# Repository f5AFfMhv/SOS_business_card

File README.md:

# SOS Business Card PCB

This project was conceived for the [Hackaday 2024 Business Card Contest](https://hackaday.io/contest/195949-2024-business-card-contest). The idea was to create a logical circuit from discrete components that would generate a SOS signal in Morse code. I wanted to make this project a learning experience for creating logical circuits in a simple and practical way.

## Logical Circuit Design

Morse code has following rules for signaling:

- dot is 1 time unit
- dash is 3 time units
- the space between symbols of the same letter is 1 time unit
- the space between words is 7 time units.

Following these rules SOS signal timing diagram will look like this:

> Diagram is made with [wavedrom online tool](https://wavedrom.com/editor.html). You can import json file from `Design/Wavedrom` for modifications.

We see that 34 independent logical states are needed. This introduces a problem as we could reduce logical circuit complexity by using 32 states instead as it will require 5 inputs for our truth table $(2^5=32)$.

I decided to violate last Morse code signaling rule and use 5 time units for spacing between words instead of 7.

I'm using [Logism](http://www.cburch.com/logisim/), it can take truth table as input and generate logical circuit. You can find Logism circuit files in `Design/Logism` directory. Generated circuit is not perfect and can be improved manually (by removing duplicated components and changing number of inputs for logical gates).

<div align="center">
    
</div>

## Clock Circuit Design

For clock signal I'm using 555 timer. There are lots of tools online for calculating 555 timer circuit parameters. I used [555 Astable Circuit Calculator ](https://ohmslawcalculator.com/555-astable-calculator) for this.

General rules are:

- choose R2 value much higher than R1 for 50% duty cycle;
- C9 sets clock frequency. 330nF capacitor will generate 2Hz signal. To increase frequency, decrease C9 value.

<div align="center">
    
</div>

For generating 5-bit logic circuit input signal we'll need binary counter. It will divide clock signal frequency by 2/4/8/16 and so on.

Full circuit simulation with 555 clock generator, binary counter and logical circuit was done using [Falstad](https://tinyurl.com/2bdrotlr). If link doesn't work, you can find Falstad circuit file in `Design/Falstad` directory.

## Power

Circuit will have 2 power options:

- CR2025 coin battery
- USB-C 5V@3A

USB-C socket CC lines are connected to ground via 5.1K ohm resistor. This tells power source to supply 5V on VBUS line. Most ICs I chose have maximum supply voltage of 6V.

## Output

The circuit will have a small on-board LED for SOS signal output. Additionally, a high-side PMOS load switch can be connected to a larger load, such as a 12V lamp. An external power supply with a maximum of 40V will be needed for this.

<div align="center">
    
</div>

## PCB Design

PCB is designed using KiCAD. All project and gerber files are in `KiCAD` directory.
Full [schematic](schematic.pdf) exported as pdf.

There are some custom symbols and footprints used in this project. Those can be imported from [this](https://github.com/f5AFfMhv/my-kicad-libraries) github repository.

## Finished Project

<div align="center">
    
</div>

Youtube video.

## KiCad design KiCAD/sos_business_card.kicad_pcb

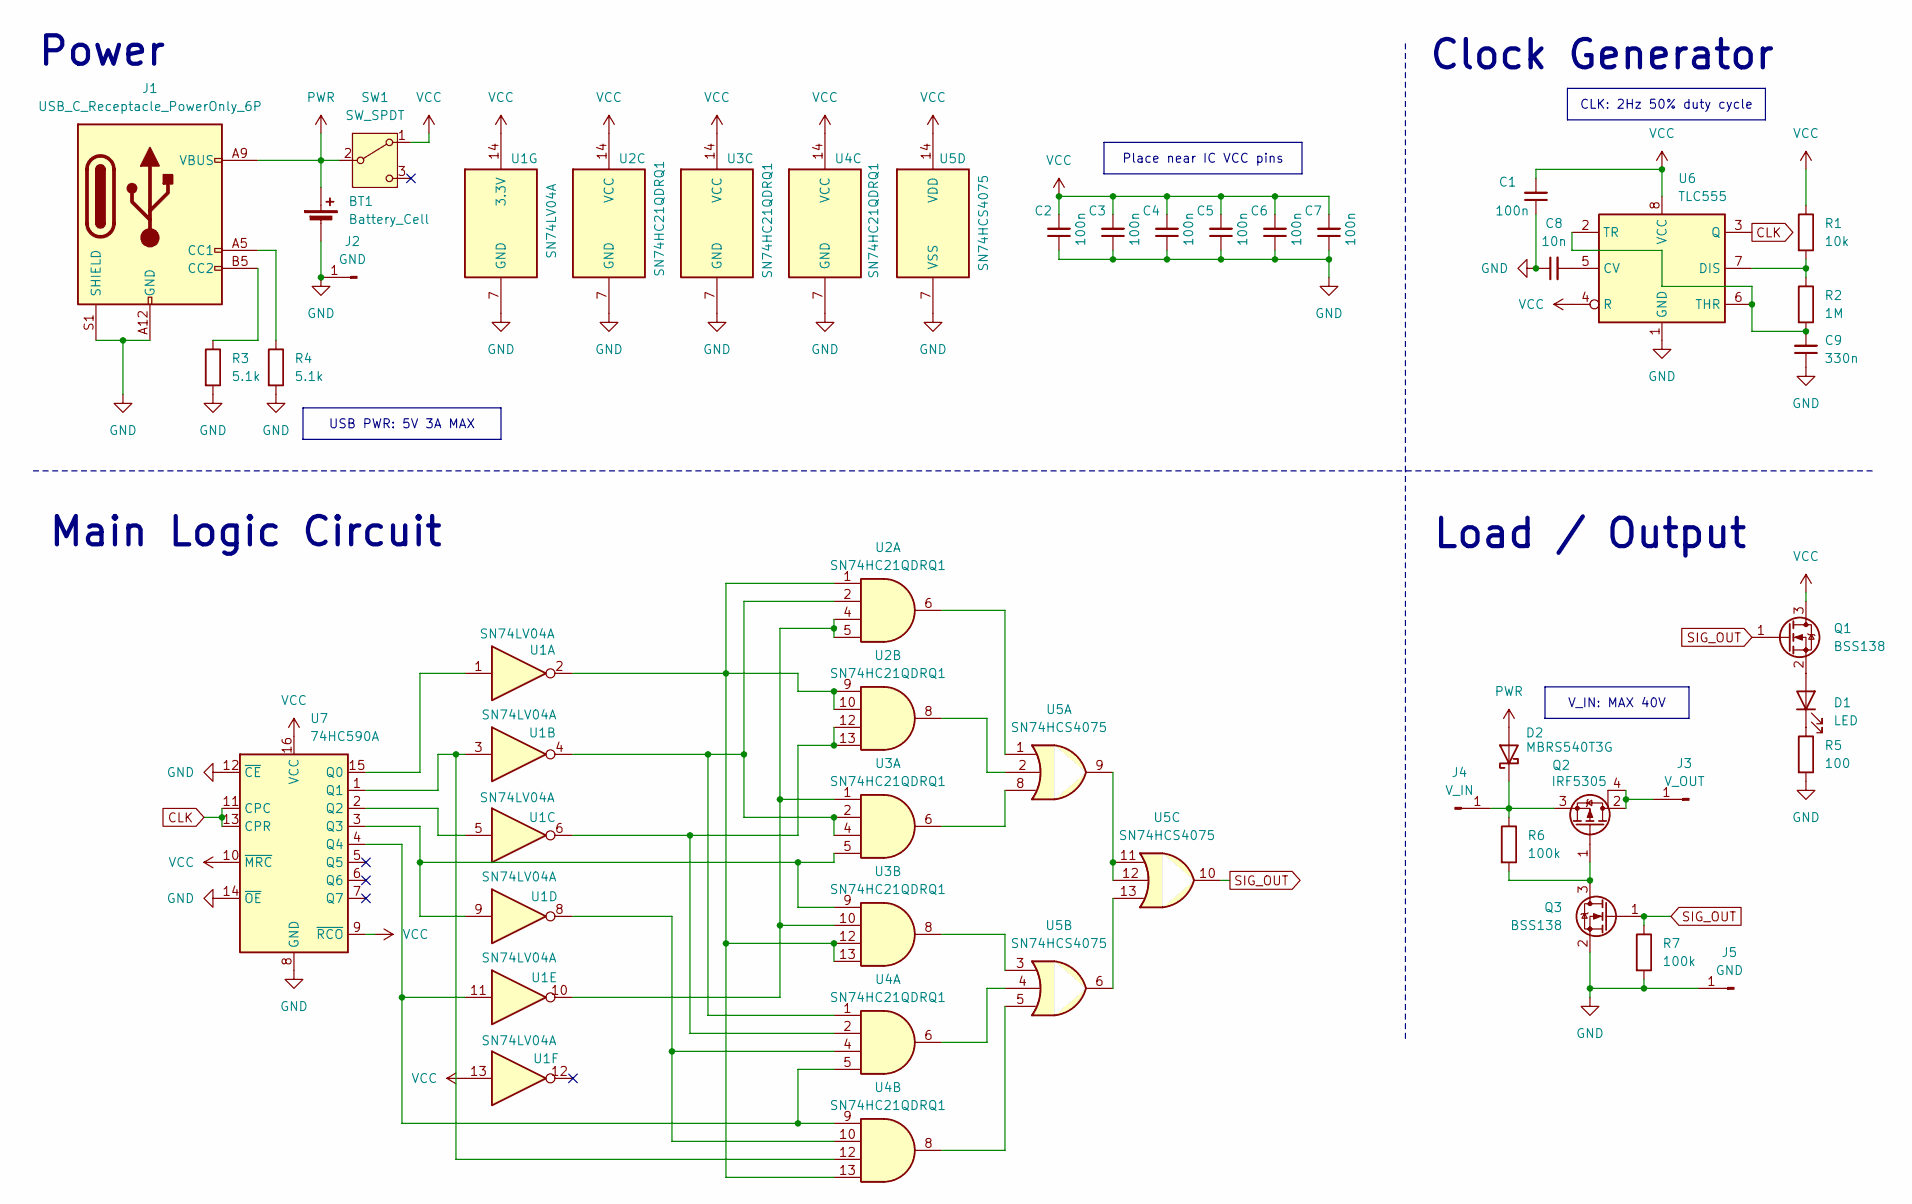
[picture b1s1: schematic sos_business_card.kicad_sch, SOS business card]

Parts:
BT1: Battery_Cell; BatteryHolder_Keystone_3034_1x20mm
C1, C2, C3, C4, C5, C6, C7: 100n; C_0805_2012Metric
C8: 10n; C_0805_2012Metric
C9: 330n; C_0805_2012Metric
D1: LED; LED_1206_3216Metric
D2: MBRS540T3G; D_SMC
J1: USB_C_Receptacle_PowerOnly_6P; USB_C_Receptacle_GCT_USB4125-xx-x_6P_TopMnt_Horizontal
J2, J5: GND; MountingHole_2.5mm_Pad_TopBottom
J3: V_OUT; MountingHole_2.5mm_Pad_TopBottom
J4: V_IN; MountingHole_2.5mm_Pad_TopBottom
Q1, Q3: BSS138; SOT-23
Q2: IRF5305; TO-220-3_Horizontal_TabDown_2
R1: 10k; R_0805_2012Metric
R2: 1M; R_0805_2012Metric
R3, R4: 5.1k; R_0805_2012Metric
R5: 100; R_0805_2012Metric
R6, R7: 100k; R_0805_2012Metric
SW1: SW_SPDT; SW_SPDT_PCM12
U1: SN74LV04A; SOIC-14_3.9x8.7mm_P1.27mm
U2, U3, U4: SN74HC21QDRQ1; SOIC-14_3.9x8.7mm_P1.27mm
U5: SN74HCS4075; SOIC-14_3.9x8.7mm_P1.27mm
U6: TLC555; SOIC-8_3.9x4.9mm_P1.27mm
U7: 74HC590A; SOIC-16W_7.5x10.3mm_P1.27mm

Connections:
CLK: U6.3 (Q), U7.11 (CPC), U7.13 (CPR)
GND: BT1.2 (-), C1.1, C2.1, C3.1, C4.1, C5.1, C6.1, C7.1, C8.1, C9.1, J1.A12 (GND), J1.B12 (GND), J1.S1 (SHIELD), J2.1, J5.1, Q3.2 (S), R3.2, R4.2, R5.2, R7.2, U1.7 (GND), U2.7 (GND), U3.7 (GND), U4.7 (GND), U5.7 (VSS), U6.1 (GND), U7.8 (GND), U7.12 (~CE), U7.14 (~OE)
unnamed: D1.2 (A), Q1.2 (S)
unnamed: D1.1 (K), R5.1
unnamed: D2.1 (K), J4.1, Q2.3 (S), R6.1
unnamed: J1.A5 (CC1), R4.1
unnamed: J1.B5 (CC2), R3.1
unnamed: J3.1, Q2.2 (D), Q2.4 (D)
unnamed: Q2.1 (G), Q3.3 (D), R6.2
unnamed: U1.2, U2.1, U2.9, U2.10, U3.12, U3.13, U4.13
unnamed: U1.4, U2.2, U3.2, U3.4, U4.1
unnamed: U1.6, U2.12, U2.13, U4.2
unnamed: U1.8, U4.4, U4.10
unnamed: U1.10, U2.4, U2.5, U3.1, U3.10
unnamed: U2.6, U5.1
unnamed: U2.8, U5.2
unnamed: U3.6, U5.8
unnamed: U3.8, U5.3
unnamed: U4.6, U5.4
unnamed: U4.8, U5.5
unnamed: U5.9, U5.11, U5.12
unnamed: U5.6, U5.13
unnamed: C8.2, U6.5 (CV)
unnamed: R1.2, R2.1, U6.7 (DIS)
unnamed: C9.2, R2.2, U6.2 (TR), U6.6 (THR)
unnamed: U1.1, U7.15 (Q0)
unnamed: U1.3, U4.12, U7.1 (Q1)
unnamed: U1.5, U7.2 (Q2)
unnamed: U1.9, U3.5, U3.9, U7.3 (Q3)
unnamed: U1.11, U4.5, U4.9, U7.4 (Q4)
PWR: BT1.1 (+), D2.2 (A), J1.A9 (VBUS), J1.B9 (VBUS), SW1.2 (B)
SIG_OUT: Q1.1 (G), Q3.1 (G), R7.1, U5.10
VCC: C1.2, C2.2, C3.2, C4.2, C5.2, C6.2, C7.2, Q1.3 (D), R1.1, SW1.1 (A), U1.13, U1.14 (3.3V), U2.14 (VCC), U3.14 (VCC), U4.14 (VCC), U5.14 (VDD), U6.4 (R), U6.8 (VCC), U7.9 (~RCO), U7.10 (~MRC), U7.16 (VCC)

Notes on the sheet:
V_IN: MAX 40V
CLK: 2Hz 50% duty cycle
Place near IC VCC pins
USB PWR: 5V 3A MAX
Main Logic Circuit
Clock Generator
Power
Load / Output

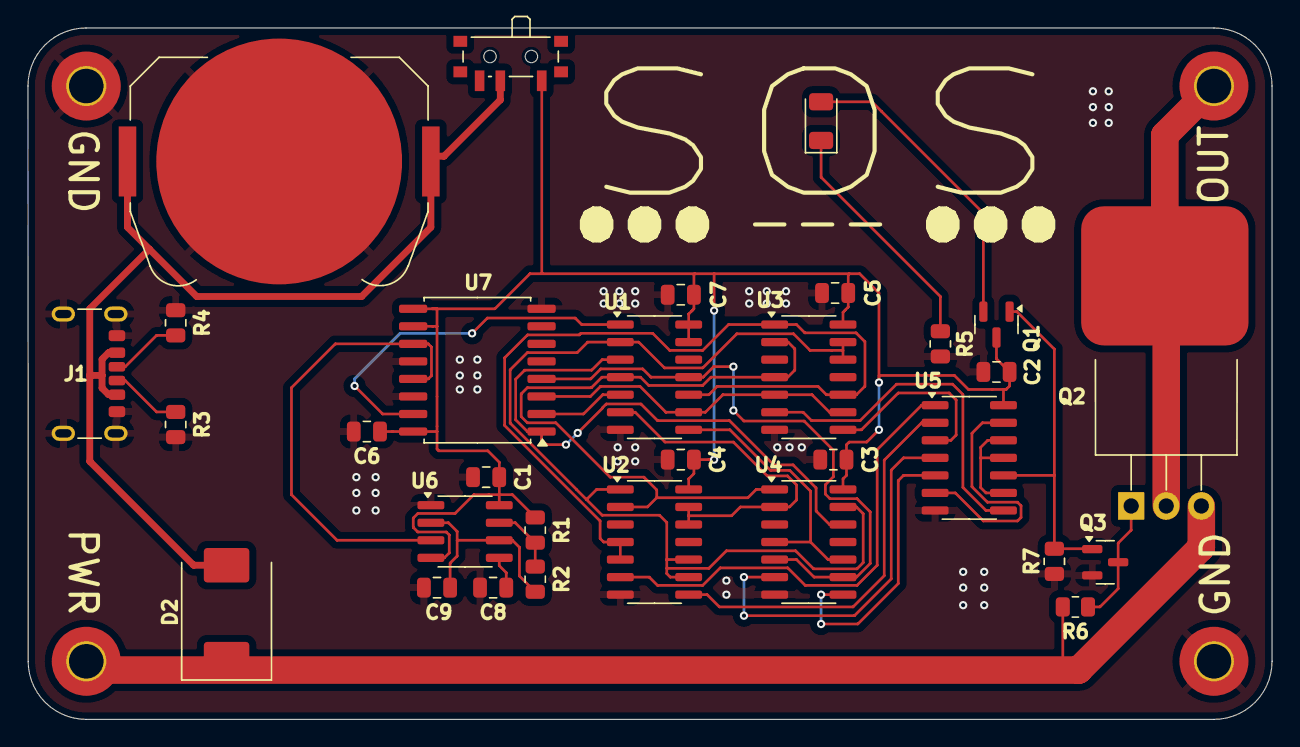
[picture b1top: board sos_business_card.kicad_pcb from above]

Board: 2 copper layers, 90.1 x 50.1 mm, 35 parts (0 on the bottom side), 33 nets.

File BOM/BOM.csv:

"Reference","Value","Datasheet","Footprint","Qty","DNP","Description"
"BT1","Battery_Cell","~","Battery:BatteryHolder_Keystone_3034_1x20mm","1","","Single-cell battery"
"C1,C2,C3,C4,C5,C6,C7","100n","~","Capacitor_SMD:C_0805_2012Metric","7","","Unpolarized capacitor, small symbol"
"C8","10n","~","Capacitor_SMD:C_0805_2012Metric","1","","Unpolarized capacitor, small symbol"
"C9","330n","~","Capacitor_SMD:C_0805_2012Metric","1","","Unpolarized capacitor, small symbol"
"D1","LED","~","LED_SMD:LED_1206_3216Metric","1","","Light emitting diode"
"D2","MBRS540T3G","https://www.onsemi.com/pdf/datasheet/mbrs540t3-d.pdf","Diode_SMD:D_SMC","1","","40V 5A Schottky Barrier Rectifier Diode, SMC"
"J1","USB_C_Receptacle_PowerOnly_6P","https://www.usb.org/sites/default/files/documents/usb_type-c.zip","Connector_USB:USB_C_Receptacle_GCT_USB4125-xx-x_6P_TopMnt_Horizontal","1","","USB Power-Only 6P Type-C Receptacle connector"
"J2,J5","GND","~","MountingHole:MountingHole_2.5mm_Pad_TopBottom","2","","Generic connector, single row, 01x01, script generated"
"J3","V_OUT","~","MountingHole:MountingHole_2.5mm_Pad_TopBottom","1","","Generic connector, single row, 01x01, script generated"
"J4","V_IN","~","MountingHole:MountingHole_2.5mm_Pad_TopBottom","1","","Generic connector, single row, 01x01, script generated"
"Q1,Q3","BSS138","https://www.onsemi.com/pub/Collateral/BSS138-D.PDF","Package_TO_SOT_SMD:SOT-23","2","","50V Vds, 0.22A Id, N-Channel MOSFET, SOT-23"
"Q2","IRF5305","https://www.infineon.com/dgdl/Infineon-IRF5305-DataSheet-v01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","my:TO-220-3_Horizontal_TabDown_2","1","","P-MOSFET transistor, gate/drain/source, drain connected to mounting plane"
"R1","10k","~","Resistor_SMD:R_0805_2012Metric","1","","Resistor"
"R2","1M","~","Resistor_SMD:R_0805_2012Metric","1","","Resistor"
"R3,R4","5.1k","~","Resistor_SMD:R_0805_2012Metric","2","","Resistor"
"R5","100","~","Resistor_SMD:R_0805_2012Metric","1","","Resistor"
"R6,R7","100k","~","Resistor_SMD:R_0805_2012Metric","2","","Resistor"
"SW1","SW_SPDT","~","Button_Switch_SMD:SW_SPDT_PCM12","1","","Switch, single pole double throw"
"U1","SN74LV04A","http://www.ti.com/lit/gpn/sn74LV04a","Package_SO:SOIC-14_3.9x8.7mm_P1.27mm","1","","Hex Inverter"
"U2,U3,U4","SN74HC21QDRQ1","https://www.ti.com/lit/ds/symlink/sn74hc21-q1.pdf","Package_SO:SOIC-14_3.9x8.7mm_P1.27mm","3","","Dual 4-input AND"
"U5","SN74HCS4075","https://www.ti.com/cn/lit/ds/symlink/sn74hcs4075.pdf","Package_SO:SOIC-14_3.9x8.7mm_P1.27mm","1","","Triple Or 3 inputs"
"U6","TLC555","https://www.ti.com/lit/ds/symlink/tlc555.pdf","Package_SO:SOIC-8_3.9x4.9mm_P1.27mm","1","","Single LinCMOS Timer, 555 compatible, SOIC-8"
"U7","74HC590A","http://www.ti.com/lit/ds/symlink/sn74hc590a.pdf","Package_SO:SOIC-16W_7.5x10.3mm_P1.27mm","1","","8-bit Binary Counter with Output Register 3-State Outputs, DIP-16/SOIC-16/SOIC-16W"

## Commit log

2024-05-28 add images
2024-05-31 fix typos
2024-05-31 update gitignore
2024-05-31 update BOM
2024-06-23 add finished project details
2026-01-01 add workflow
2026-01-01 update wf
